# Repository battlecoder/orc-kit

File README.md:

# orc-kit
Open Source (and Hardware) Robotics Project.

Folder Content:
<ul>
<li><b>dist:</b> 3D models and vector patterns in "ready to use" formats (DXF and STL). Instructional sheet inside.</li>
<li><b>arduino:</b> Arduino libraries and example sketches for starters.</li>
<li><b>pcbs:</b> Eagle file and PNG render for the project custom circuit boards (Optional content)</li>
<li><b>vector-models:</b> "Source" files for the vector drawings and pieces (in SVG format)</li>
<li><b>3d pieces:</b> "Source" files for the 3D models (in SketchUp format)</li>
</ul>

For more information visit <a href="http://damnsoft.org/orc-kit">damnsoft.org/orc-kit</a>.

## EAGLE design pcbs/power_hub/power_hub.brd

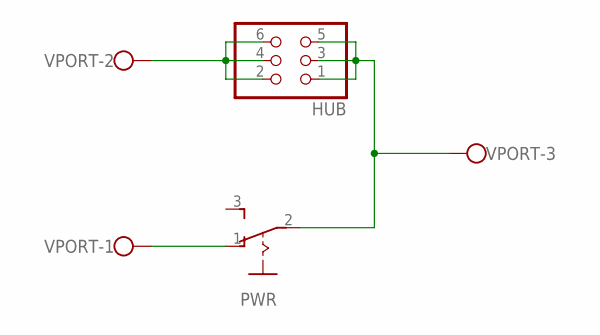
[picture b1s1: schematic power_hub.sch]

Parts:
HUB: PINHD-2X3; 2X03
PWR: M251
VPORT: W237-103

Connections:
unnamed: PWR.1 (O), VPORT.1
unnamed: HUB.1, HUB.3, HUB.5, PWR.2, VPORT.3
unnamed: HUB.2, HUB.4, HUB.6, VPORT.2

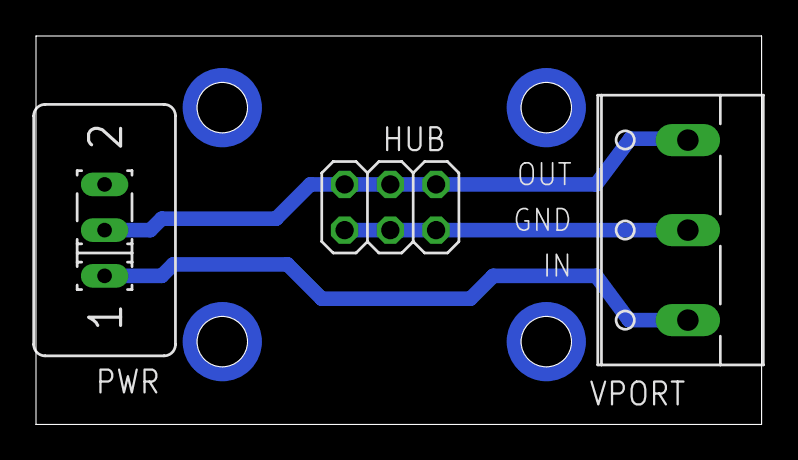
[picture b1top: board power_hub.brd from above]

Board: 2 copper layers, 40.3 x 21.6 mm, 3 parts (0 on the bottom side), 3 nets.

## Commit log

2016-10-09 All files pushed to repository
2016-10-09 Updated README.
2016-10-09 Added comments to reflect github release
2016-10-15 Updated model reference with correct base frame thickness (4mm)
2016-12-19 Refactored the Arduino code so it can be imported as a library from the IDE. Added an HBridge driver fully compatible with the previous Motorshield controller. Modified the Radiocontrol class and exa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
